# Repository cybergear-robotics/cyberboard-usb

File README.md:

# CyberBoard - USB

This is the Kicad project for the CyberBoard. It has an ESP32S3 which is
connected via USB to a computer. The microcontroller drives the cybergear 
motors via CAN. Furthermore a MOLEX CLIK connector is integrated in order
to communicate with the power distribution board [Holybro PM03D Pixhawk 5X Power
Module](https://docs.holybro.com/power-module-and-pdb/power-module/digital-power-module-pm-setup).
This board does not only provides six XT-30 connectors for each cybergear motor,
but also an INA226 i2c power monitor unit. The IMU ICM20948 is integrated on the
CyberBoard.

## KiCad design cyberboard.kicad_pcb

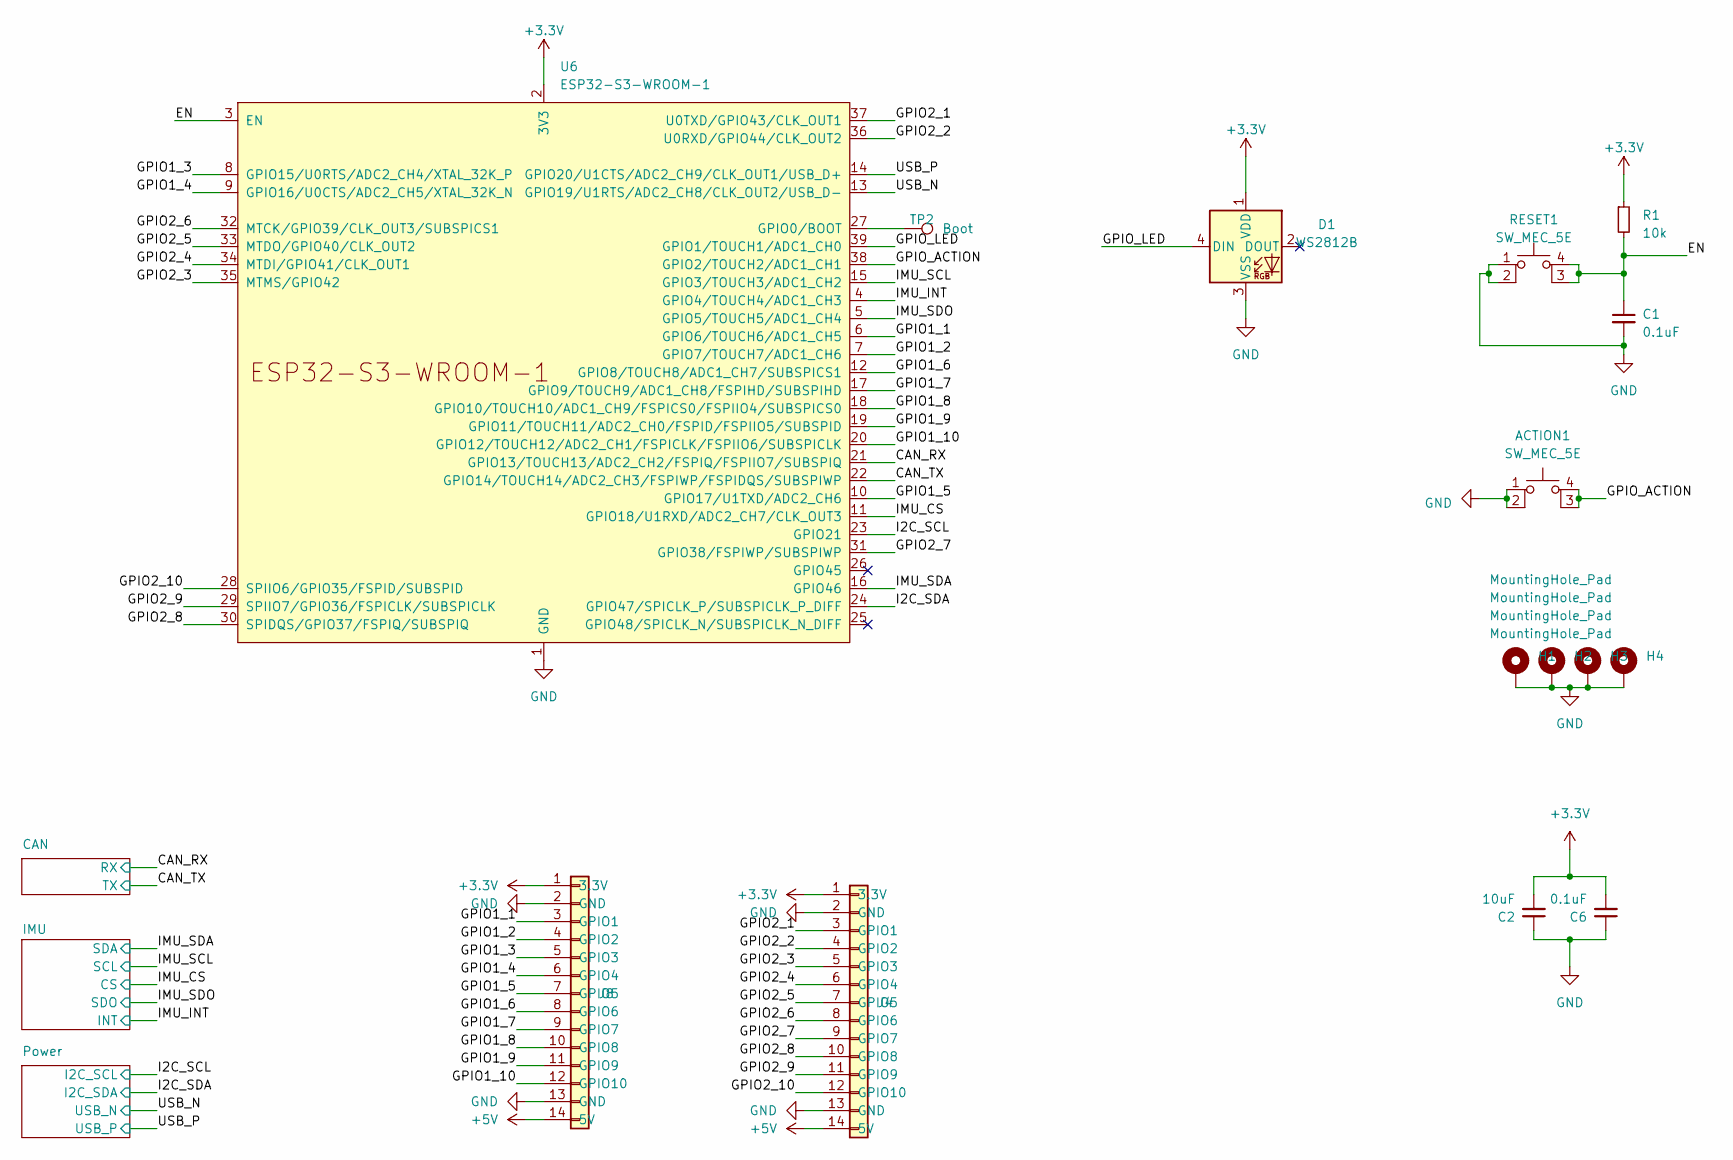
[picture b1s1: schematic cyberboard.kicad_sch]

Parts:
ACTION1: SW_MEC_5E; SW_Push_1P1T_XKB_TS-1187A; LCSC C318884
C1, C6: 0.1uF; C_0805_2012Metric; LCSC C49678
C2: 10uF; C_0805_2012Metric; LCSC C15850
D1: WS2812B; LED_WS2812B_PLCC4_5.0x5.0mm_P3.2mm
H1, H2, H3, H4: MountingHole_Pad; MountingHole_3.2mm_M3_DIN965_Pad
J4, J8: Conn_01x14; PinSocket_1x14_P2.54mm_Vertical
R1: 10k; R_0805_2012Metric; LCSC C17414
RESET1: SW_MEC_5E; SW_Push_1P1T_XKB_TS-1187A; LCSC C318884
TP2: Boot; TestPoint_Pad_1.0x1.0mm
U6: ESP32-S3-WROOM-1; ESP32-S3-WROOM-1U

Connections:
+3.3V: C2.2, C6.2, D1.1 (VDD), J4.1 (3.3V), J8.1 (3.3V), R1.1, U6.2 (3V3); also elsewhere on the board
+5V: J4.14 (5V), J8.14 (5V); also elsewhere on the board
/CAN_RX: U6.21 (GPIO13/TOUCH13/ADC2_CH2/FSPIQ/FSPIIO7/S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); also elsewhere on the board
/CAN_TX: U6.22 (GPIO14/TOUCH14/ADC2_CH3/FSPIWP/FSPIDQS/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); also elsewhere on the board
/EN: C1.1, R1.2, RESET1.3 (K), RESET1.4 (A), U6.3 (EN)
/GPIO1_1: J8.3 (GPIO1), U6.6 (GPIO6/TOUCH6/ADC1_CH5)
/GPIO1_2: J8.4 (GPIO2), U6.7 (GPIO7/TOUCH7/ADC1_CH6)
/GPIO1_3: J8.5 (GPIO3), U6.8 (GPIO15/U0RTS/ADC2_CH4/XTAL_32K_P)
/GPIO1_4: J8.6 (GPIO4), U6.9 (GPIO16/U0CTS/ADC2_CH5/XTAL_32K_N)
/GPIO1_5: J8.7 (GPIO5), U6.10 (GPIO17/U1TXD/ADC2_CH6)
/GPIO1_6: J8.8 (GPIO6), U6.12 (GPIO8/TOUCH8/ADC1_CH7/SUBSPICS1)
/GPIO1_7: J8.9 (GPIO7), U6.17 (GPIO9/TOUCH9/ADC1_CH8/FSPIHD/SUBSPIHD)
/GPIO1_8: J8.10 (GPIO8), U6.18 (GPIO10/TOUCH10/ADC1_CH9/FSPICS0/FSPIIO4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)
/GPIO1_9: J8.11 (GPIO9), U6.19 (GPIO11/TOUCH11/ADC2_CH0/FSPID/FSPIIO5/S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)
/GPIO1_10: J8.12 (GPIO10), U6.20 (GPIO12/TOUCH12/ADC2_CH1/FSPICLK/FSPIIO6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)
/GPIO2_1: J4.3 (GPIO1), U6.37 (U0TXD/GPIO43/CLK_OUT1)
/GPIO2_2: J4.4 (GPIO2), U6.36 (U0RXD/GPIO44/CLK_OUT2)
/GPIO2_3: J4.5 (GPIO3), U6.35 (MTMS/GPIO42)
/GPIO2_4: J4.6 (GPIO4), U6.34 (MTDI/GPIO41/CLK_OUT1)
/GPIO2_5: J4.7 (GPIO5), U6.33 (MTDO/GPIO40/CLK_OUT2)
/GPIO2_6: J4.8 (GPIO6), U6.32 (MTCK/GPIO39/CLK_OUT3/SUBSPICS1)
/GPIO2_7: J4.9 (GPIO7), U6.31 (GPIO38/FSPIWP/SUBSPIWP)
/GPIO2_8: J4.10 (GPIO8), U6.30 (SPIDQS/GPIO37/FSPIQ/SUBSPIQ)
/GPIO2_9: J4.11 (GPIO9), U6.29 (SPIIO7/GPIO36/FSPICLK/SUBSPICLK)
/GPIO2_10: J4.12 (GPIO10), U6.28 (SPIIO6/GPIO35/FSPID/SUBSPID)
/GPIO_ACTION: ACTION1.3 (K), ACTION1.4 (A), U6.38 (GPIO2/TOUCH2/ADC1_CH1)
/GPIO_LED: D1.4 (DIN), U6.39 (GPIO1/TOUCH1/ADC1_CH0)
/I2C_SCL: U6.23 (GPIO21); also elsewhere on the board
/I2C_SDA: U6.24 (GPIO47/SPICLK_P/SUBSPICLK_P_DIFF); also elsewhere on the board
/IMU_CS: U6.11 (GPIO18/U1RXD/ADC2_CH7/CLK_OUT3); also elsewhere on the board
/IMU_INT: U6.4 (GPIO4/TOUCH4/ADC1_CH3); also elsewhere on the board
/IMU_SCL: U6.15 (GPIO3/TOUCH3/ADC1_CH2); also elsewhere on the board
/IMU_SDA: U6.16 (GPIO46); also elsewhere on the board
/IMU_SDO: U6.5 (GPIO5/TOUCH5/ADC1_CH4); also elsewhere on the board
/USB_N: U6.13 (GPIO19/U1RTS/ADC2_CH8/CLK_OUT2/USB_D-); also elsewhere on the board
/USB_P: U6.14 (GPIO20/U1CTS/ADC2_CH9/CLK_OUT1/USB_D+); also elsewhere on the board
GND: ACTION1.1, ACTION1.2, C1.2, C2.1, C6.1, D1.3 (VSS), H1.1, H2.1, H3.1, H4.1, J4.2 (GND), J4.13 (GND), J8.2 (GND), J8.13 (GND), RESET1.1, RESET1.2, U6.1 (GND), U6.40 (GND), U6.41 (GND); also elsewhere on the board
unnamed: TP2.1, U6.27 (GPIO0/BOOT)

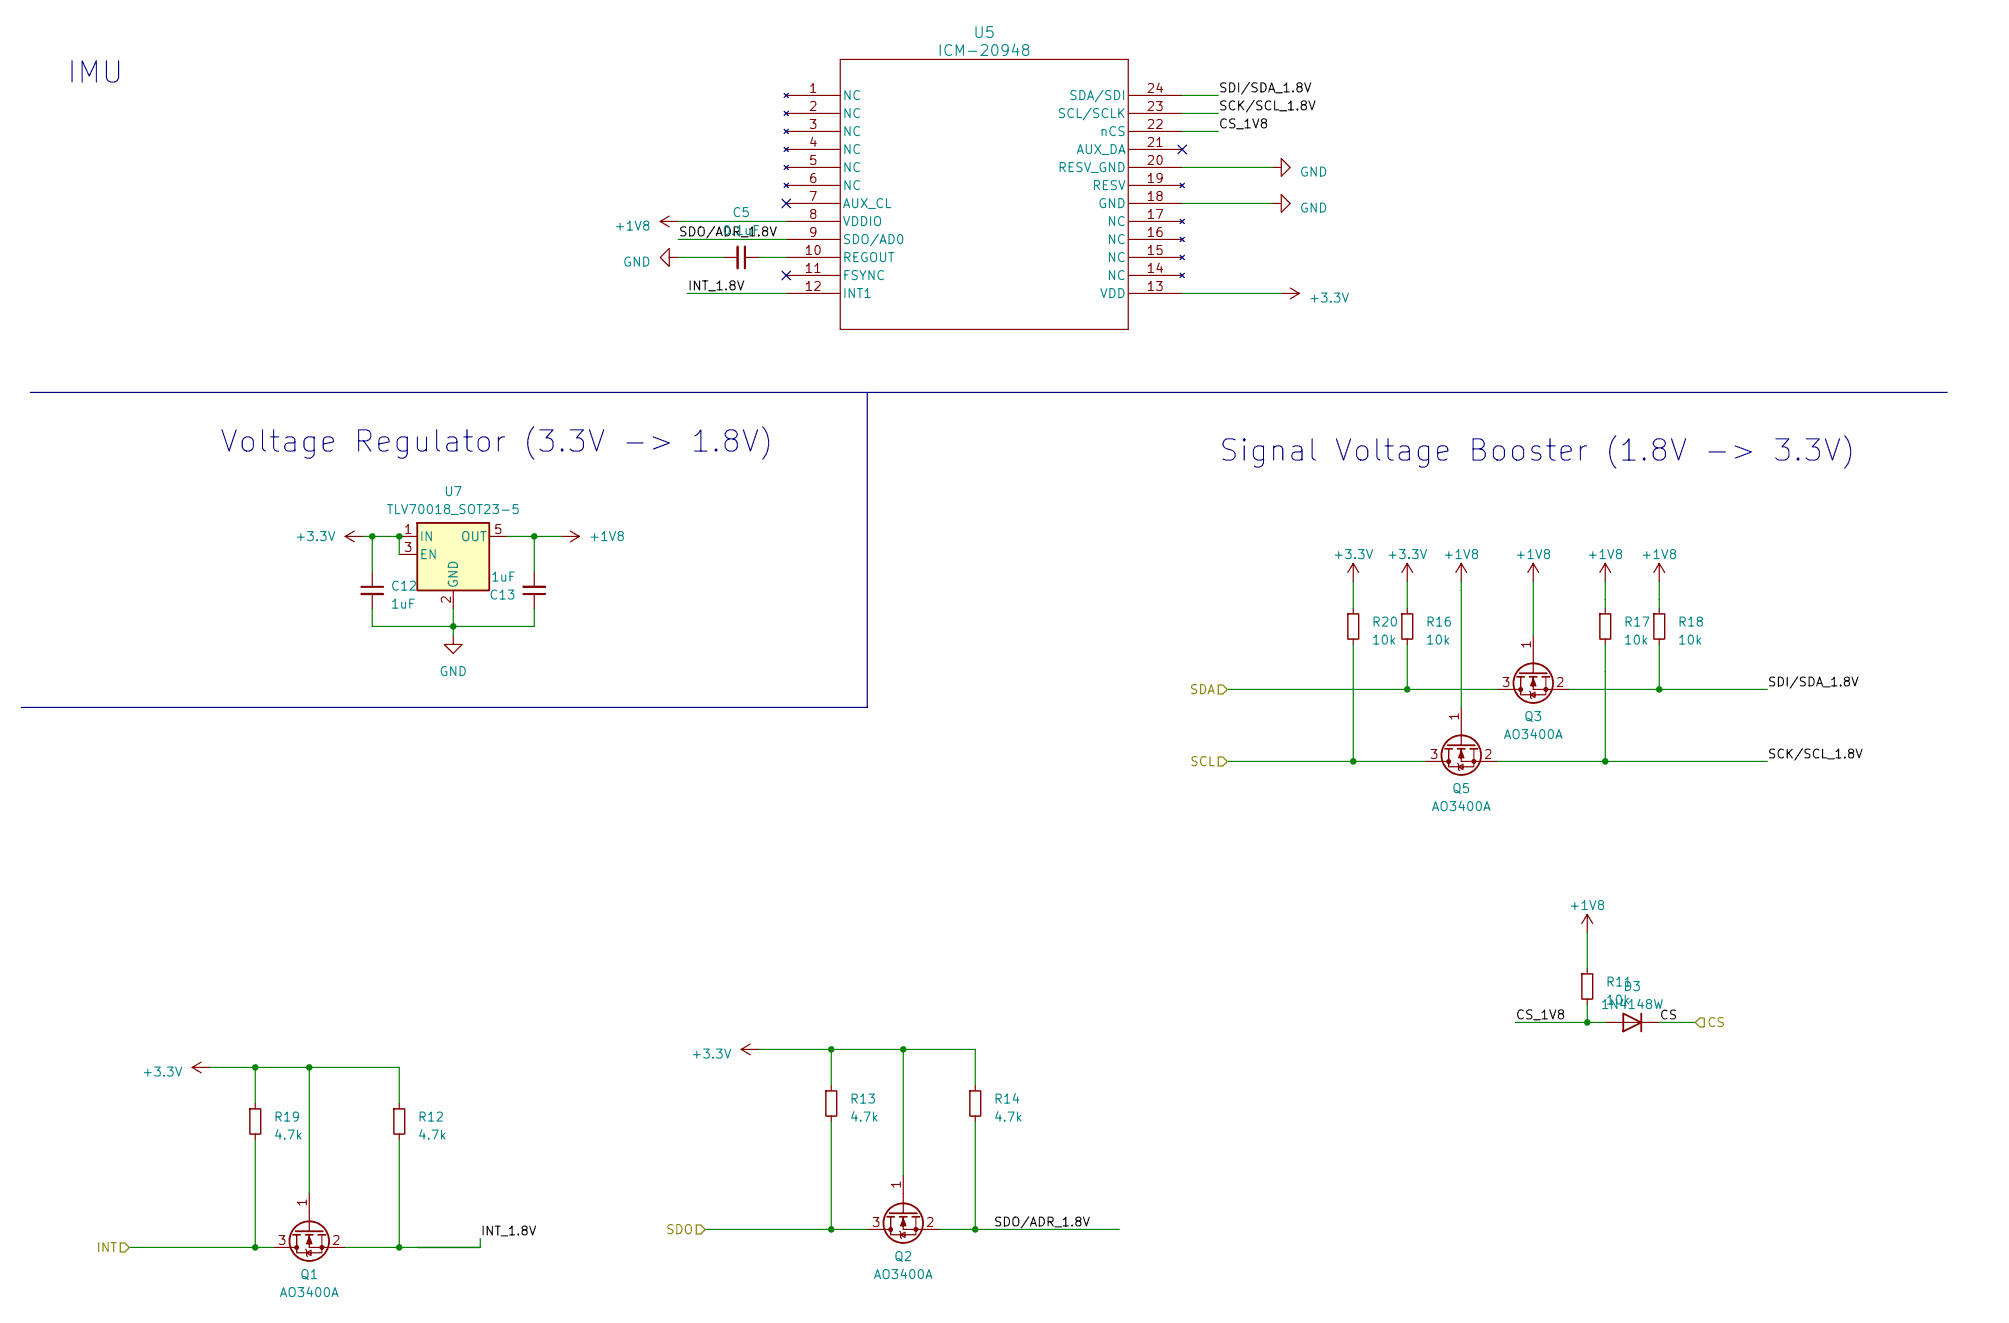
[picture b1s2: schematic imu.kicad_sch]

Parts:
C5: 0.1uF; C_0805_2012Metric; LCSC C49678
C12, C13: 1uF; C_0805_2012Metric; LCSC C28323
D3: 1N4148W; D_SOD-123; LCSC C81598
Q1, Q2, Q3, Q5: AO3400A; SOT-23; LCSC C20917
R11, R16, R17, R18, R20: 10k; R_0805_2012Metric; LCSC C17414
R12, R13, R14, R19: 4.7k; R_0805_2012Metric; LCSC C17673
U5: ICM-20948; QFN24_3X3X0P9_IVS; LCSC C726001
U7: TLV70018_SOT23-5; SOT-23-5; LCSC C79924

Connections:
+1V8: C13.2, Q3.1 (G), Q5.1 (G), R11.1, R17.1, R18.1, U5.8 (VDDIO), U7.5 (OUT)
+3.3V: C12.1, Q1.1 (G), Q2.1 (G), R12.1, R13.1, R14.1, R16.1, R19.1, R20.1, U5.13 (VDD), U7.1 (IN), U7.3 (EN); also elsewhere on the board
/IMU/CS_1V8: D3.2 (A), R11.2, U5.22 (nCS)
/IMU/INT_1.8V: Q1.2 (S), R12.2, U5.12 (INT1)
/IMU_CS: D3.1 (K); also elsewhere on the board
/IMU_INT: Q1.3 (D), R19.2; also elsewhere on the board
/IMU_SCL: Q5.3 (D), R20.2; also elsewhere on the board
/IMU_SDA: Q3.3 (D), R16.2; also elsewhere on the board
/IMU_SDO: Q2.3 (D), R13.2; also elsewhere on the board
GND: C5.2, C12.2, C13.1, U5.18 (GND), U5.20 (RESV_GND), U7.2 (GND); also elsewhere on the board
unnamed: C5.1, U5.10 (REGOUT)

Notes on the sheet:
IMU
Signal Voltage Booster (1.8V -> 3.3V)
Voltage Regulator (3.3V -> 1.8V)

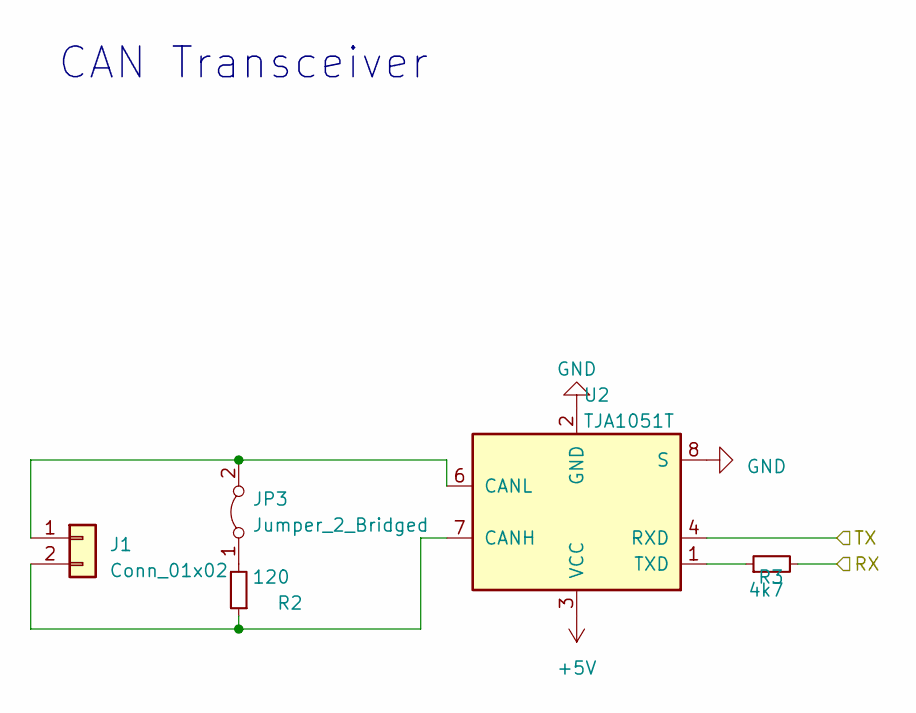
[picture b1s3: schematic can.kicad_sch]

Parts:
J1: Conn_01x02; JST_XH_S2B-XH-A-1_1x02_P2.50mm_Horizontal
JP3: Jumper_2_Bridged; PinHeader_1x02_P2.00mm_Vertical
R2: 120; R_0805_2012Metric; LCSC C17437
R3: 4k7; R_0805_2012Metric; LCSC C17673
U2: TJA1051T; SOIC-8_3.9x4.9mm_P1.27mm; LCSC C92211

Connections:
+5V: U2.3 (VCC); also elsewhere on the board
/CAN_RX: R3.2; also elsewhere on the board
/CAN_TX: U2.4 (RXD); also elsewhere on the board
GND: U2.2 (GND), U2.8 (S); also elsewhere on the board
unnamed: J1.1, JP3.2 (B), U2.6 (CANL)
unnamed: J1.2, R2.1, U2.7 (CANH)
unnamed: JP3.1 (A), R2.2
unnamed: R3.1, U2.1 (TXD)

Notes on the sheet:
CAN Transceiver

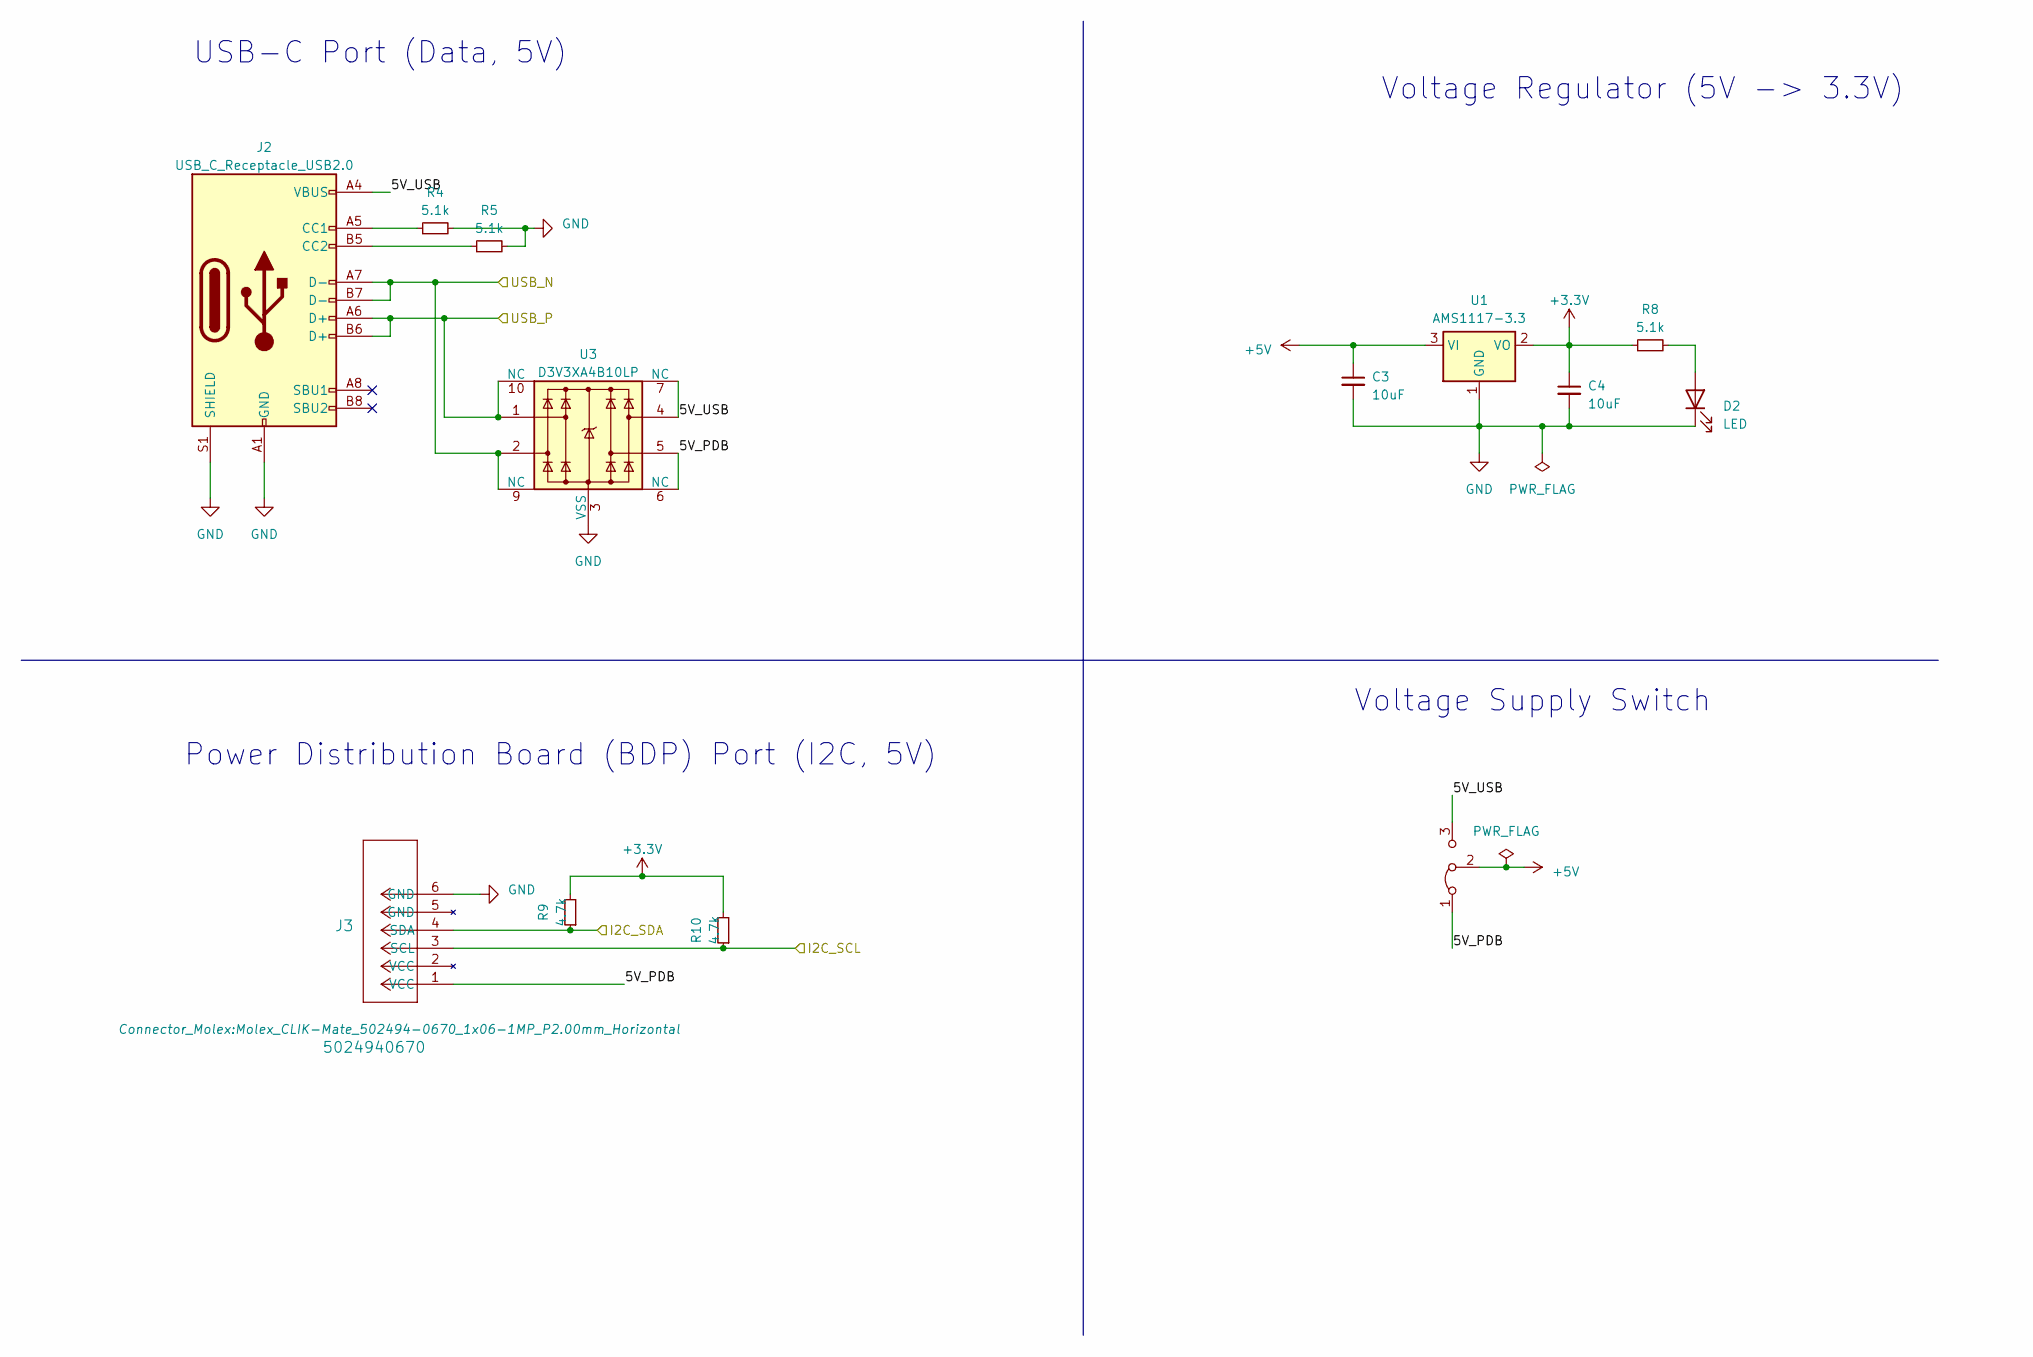
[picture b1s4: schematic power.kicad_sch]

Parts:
C3, C4: 10uF; C_0805_2012Metric; LCSC C15850
D2: LED; LED_0603_1608Metric; LCSC C2286
J2: USB_C_Receptacle_USB2.0; USB_C_Receptacle_HRO_TYPE-C-31-M-12; LCSC C165948
J3: 5024940670; Molex_CLIK-Mate_502494-0670_1x06-1MP_P2.00mm_Horizontal; LCSC C587930
JP1: Jumper_3_Bridged12; PinHeader_1x03_P2.00mm_Vertical
R4, R5, R8: 5.1k; R_0805_2012Metric; LCSC C27834
R9, R10: 4.7k; R_0805_2012Metric; LCSC C17673
U1: AMS1117-3.3; SOT-223-3_TabPin2; LCSC C6186
U3: D3V3XA4B10LP; Diodes_UDFN-10_1.0x2.5mm_P0.5mm; LCSC C1980462

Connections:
+3.3V: C4.1, R8.1, R9.2, R10.2, U1.2 (VO); also elsewhere on the board
+5V: C3.1, JP1.2 (C), U1.3 (VI); also elsewhere on the board
/I2C_SCL: J3.3 (SCL), R10.1; also elsewhere on the board
/I2C_SDA: J3.4 (SDA), R9.1; also elsewhere on the board
/Power/5V_PDB: J3.1 (VCC), JP1.1 (A), U3.5, U3.6 (NC)
/Power/5V_USB: J2.A4 (VBUS), J2.A9 (VBUS), J2.B4 (VBUS), J2.B9 (VBUS), JP1.3 (B), U3.4, U3.7 (NC)
/USB_N: J2.A7 (D-), J2.B7 (D-), U3.2, U3.9 (NC); also elsewhere on the board
/USB_P: J2.A6 (D+), J2.B6 (D+), U3.1, U3.10 (NC); also elsewhere on the board
GND: C3.2, C4.2, D2.1 (K), J2.A1 (GND), J2.A12 (GND), J2.B1 (GND), J2.B12 (GND), J2.S1 (SHIELD), J3.6 (GND), R4.2, R5.2, U1.1 (GND), U3.3 (VSS), U3.8 (VSS); also elsewhere on the board
unnamed: D2.2 (A), R8.2
unnamed: J2.A5 (CC1), R4.1
unnamed: J2.B5 (CC2), R5.1

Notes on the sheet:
USB-C Port (Data, 5V)
Voltage Regulator (5V -> 3.3V)
Power Distribution Board (BDP) Port (I2C, 5V)
Voltage Supply Switch

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
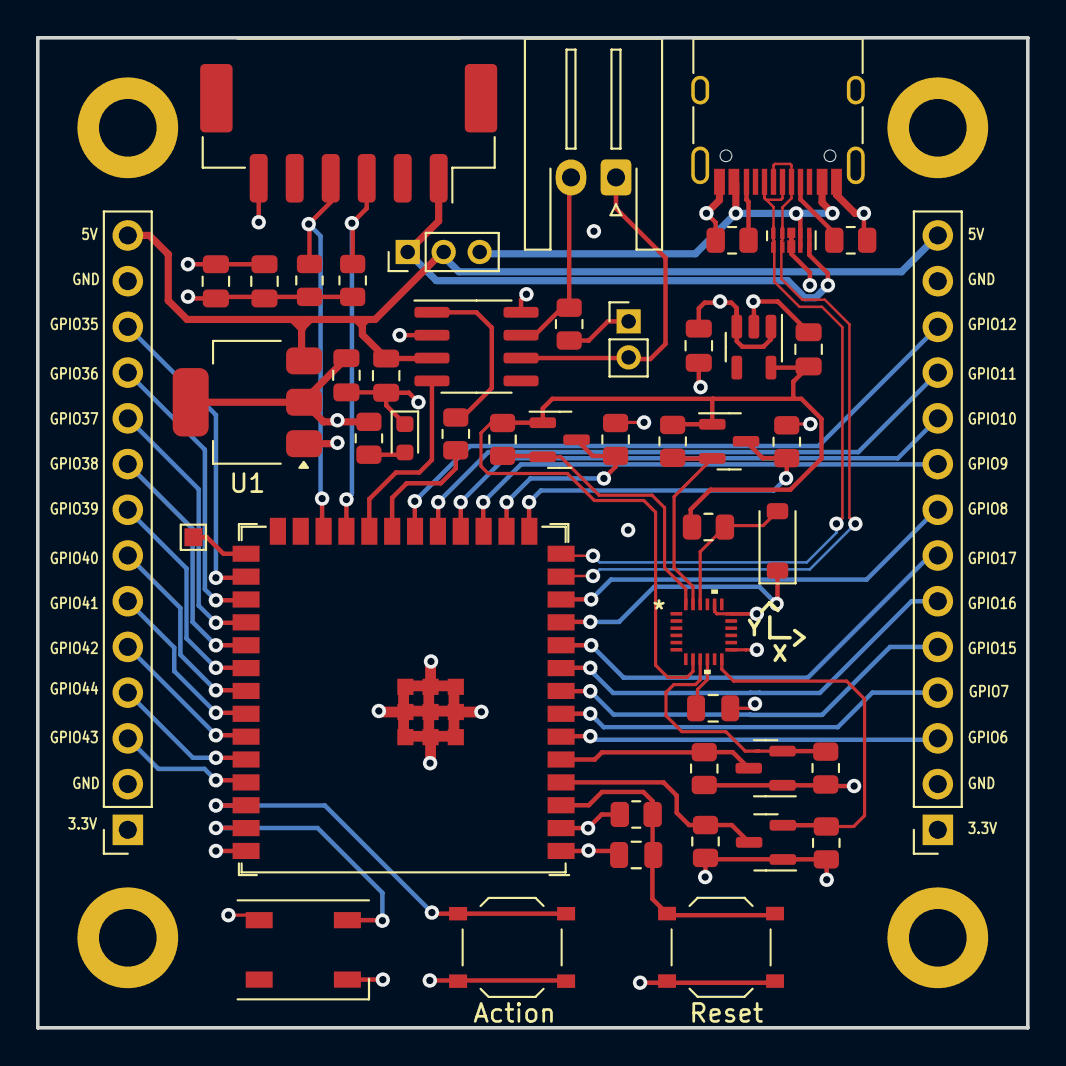
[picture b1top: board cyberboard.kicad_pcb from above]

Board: 4 copper layers, 55.0 x 55.0 mm, 52 parts (0 on the bottom side), 54 nets.

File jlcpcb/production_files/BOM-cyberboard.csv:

Comment,Designator,Footprint,LCSC
10uF,"C2,C3,C4",C_0805_2012Metric,C15850
USB_C_Receptacle_USB2.0,J2,USB_C_Receptacle_HRO_TYPE-C-31-M-12,C165948
10k,"R1,R11,R16,R17,R18,R20",R_0805_2012Metric,C17414
120,R2,R_0805_2012Metric,C17437
4.7k,"R10,R12,R13,R14,R19,R3,R9",R_0805_2012Metric,C17673
D3V3XA4B10LP,U3,Diodes_UDFN-10_1.0x2.5mm_P0.5mm,C1980462
AO3400A,"Q1,Q2,Q3,Q5",SOT-23,C20917
LED,D2,LED_0603_1608Metric,C2286
5.1k,"R4,R5,R8",R_0805_2012Metric,C27834
1uF,"C12,C13",C_0805_2012Metric,C28323
SW_MEC_5E,"ACTION1,RESET1",SW_Push_1P1T_XKB_TS-1187A,C318884
0.1uF,"C1,C5,C6",C_0805_2012Metric,C49678
5024940670,J3,Molex_CLIK-Mate_502494-0670_1x06-1MP_P2.00mm_Horizontal,C587930
AMS1117-3.3,U1,SOT-223-3_TabPin2,C6186
ICM-20948,U5,QFN24_3X3X0P9_IVS,C726001
TLV70018_SOT23-5,U7,SOT-23-5,C79924
1N4148W,D3,D_SOD-123,C81598
TJA1051T,U2,SOIC-8_3.9x4.9mm_P1.27mm,C92211

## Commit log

2024-04-26 deployment release
2025-03-30 add small changes
2025-03-30 remove release files
2025-03-30 add screenshots and license
2025-03-30 add badges

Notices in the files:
README.md:
License: MIT
